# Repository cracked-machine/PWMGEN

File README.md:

# PWMGEN

## Handheld STM32 PWM Generator

* A 10mm x 10mm x 30mm PWM signal generator with duty, prescaler and frequency control. 
* Supports both 3.3v and 5v logic level outputs.
* Output PWM can source 500mA.
* Requires a 9VDC 600mA power supply (5.5mm x 2.1mm connector, Centre-Positive).

### TODO

* 5V PSU input (remove uA78M05C)
* Increase PWM source current capabilities. (Use bigger series pass transistor and regulators)
* Improve prescaler control input (use N-times throw switch and N-times GPIO input)

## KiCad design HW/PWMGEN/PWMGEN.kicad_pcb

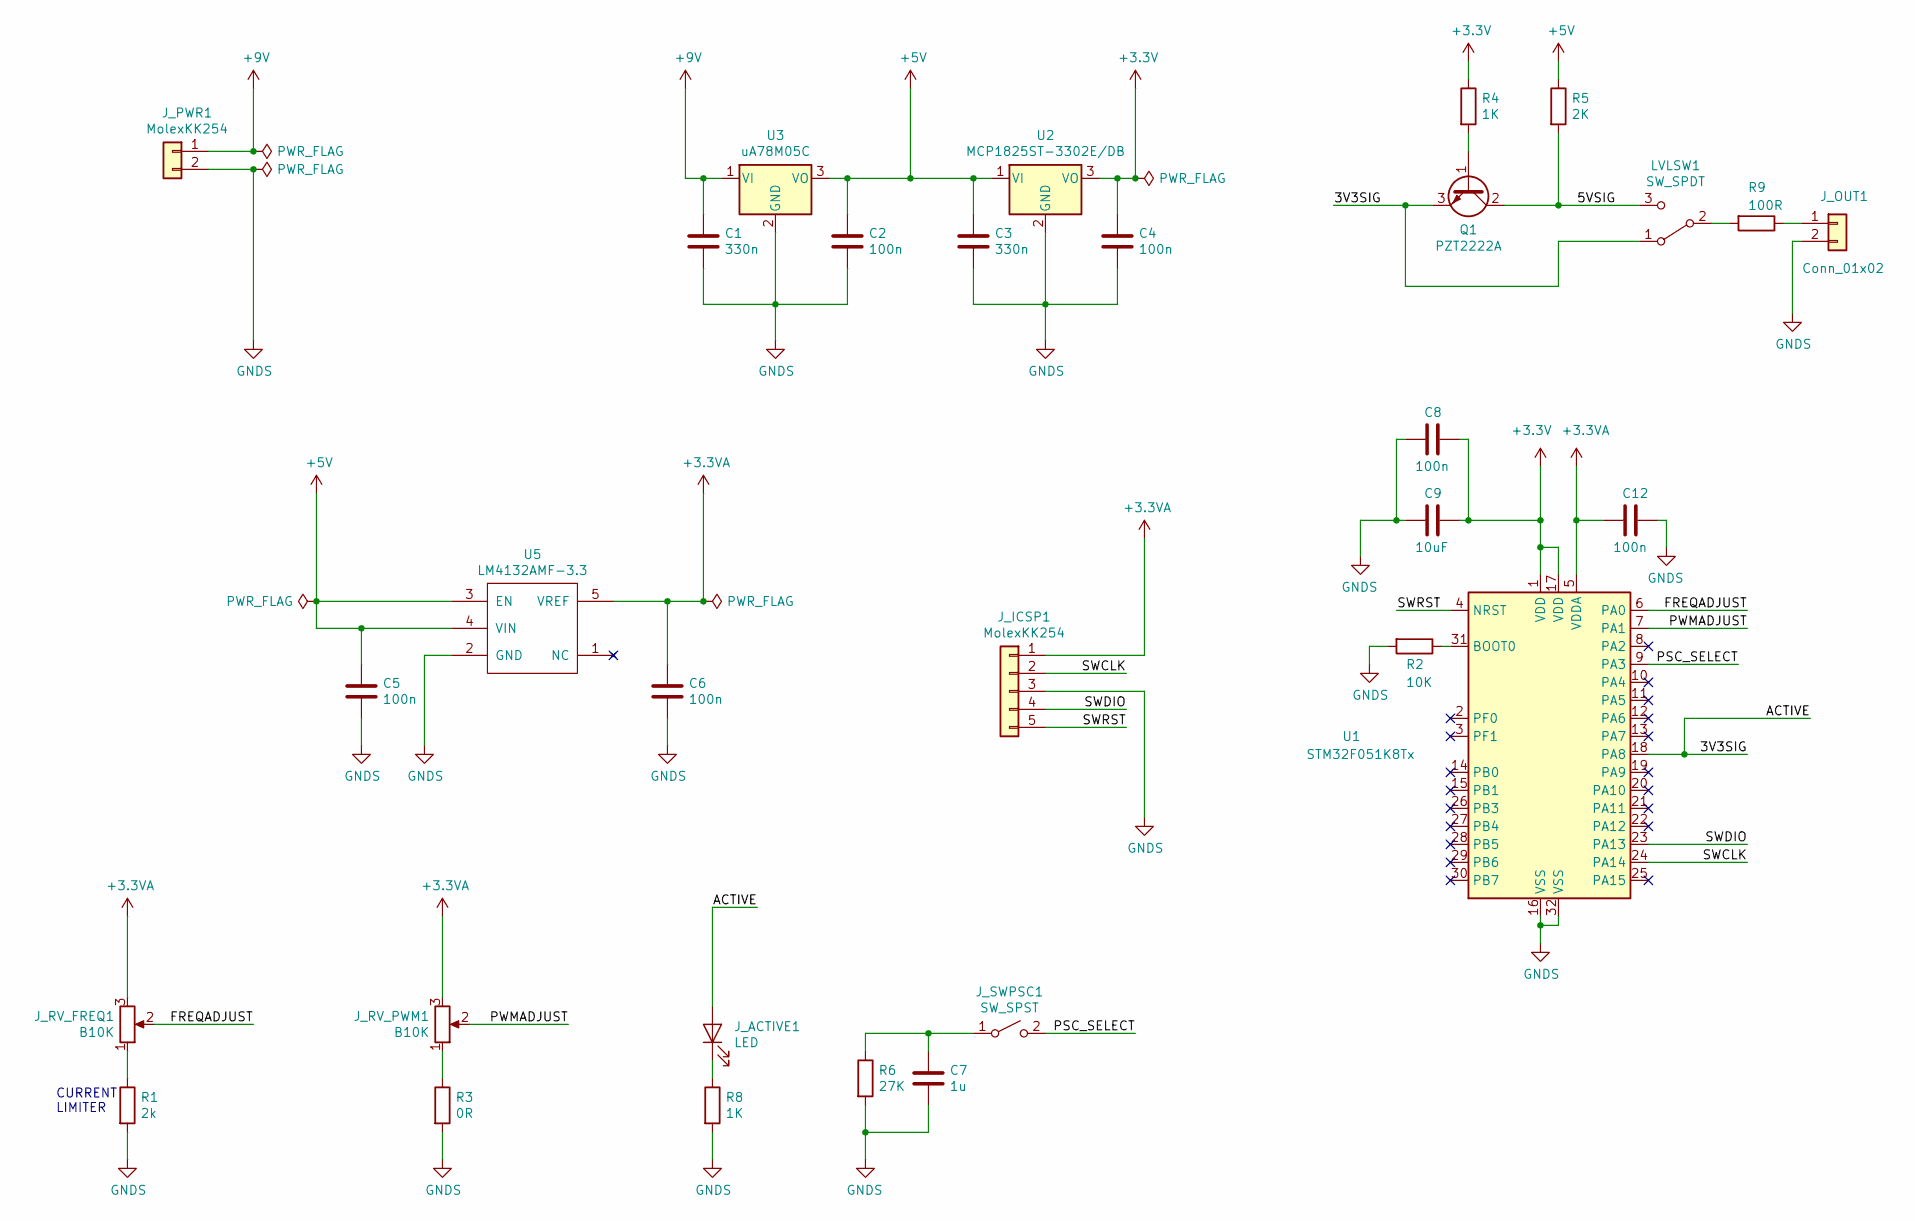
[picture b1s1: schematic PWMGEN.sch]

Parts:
C1, C3: 330n; C_1206_3216Metric_Pad1.42x1.75mm_HandSolder
C2, C4, C5, C6, C8, C12: 100n; C_1206_3216Metric_Pad1.42x1.75mm_HandSolder
C7: 1u; C_1206_3216Metric_Pad1.42x1.75mm_HandSolder
C9: 10uF; C_1206_3216Metric_Pad1.42x1.75mm_HandSolder
J_ACTIVE1: LED; PinHeader_1x02_P2.54mm_Vertical
J_ICSP1: MolexKK254; PinHeader_1x05_P2.54mm_Vertical
J_OUT1: Conn_01x02; PinHeader_1x02_P2.54mm_Vertical
J_PWR1: MolexKK254; PinHeader_1x02_P2.54mm_Vertical
J_RV_FREQ1: B10K; PinHeader_1x03_P2.54mm_Vertical
J_RV_PWM1: B10K; PinHeader_1x03_P2.54mm_Vertical
J_SWPSC1: SW_SPST; PinHeader_1x02_P2.54mm_Vertical
LVLSW1: SW_SPDT; PinHeader_1x03_P2.54mm_Vertical
Q1: PZT2222A; SOT-223
R1: 2k; R_1206_3216Metric_Pad1.42x1.75mm_HandSolder
R2: 10K; R_1206_3216Metric_Pad1.42x1.75mm_HandSolder
R3: 0R; R_1206_3216Metric_Pad1.42x1.75mm_HandSolder
R4, R8: 1K; R_1206_3216Metric_Pad1.42x1.75mm_HandSolder
R5: 2K; R_1206_3216Metric_Pad1.42x1.75mm_HandSolder
R6: 27K; R_1206_3216Metric_Pad1.42x1.75mm_HandSolder
R9: 100R; R_1206_3216Metric_Pad1.42x1.75mm_HandSolder
U1: STM32F051K8Tx; LQFP-32_7x7mm_P0.8mm
U2: MCP1825ST-3302E/DB; SOT-223-3_TabPin2
U3: uA78M05C; SOT-223-3_TabPin2
U5: LM4132AMF-3.3; SOT-23-5_HandSoldering

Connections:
+3.3VA: C6.1, C12.2, J_ICSP1.1, J_RV_FREQ1.3, J_RV_PWM1.3, U1.5 (VDDA), U5.5 (VREF)
+3V3: C4.1, C8.1, C9.1, R4.1, U1.1 (VDD), U1.17 (VDD), U2.3 (VO)
+5V: C2.1, C3.1, C5.1, R5.1, U2.1 (VI), U3.3 (VO), U5.3 (EN), U5.4 (VIN)
+9V: C1.1, J_PWR1.1, U3.1 (VI)
/3V3SIG: J_ACTIVE1.2 (A), LVLSW1.1 (A), Q1.3 (E), U1.18 (PA8)
/5VSIG: LVLSW1.3 (C), Q1.2 (C), R5.2
/FREQADJUST: J_RV_FREQ1.2, U1.6 (PA0)
/PSC_SELECT: J_SWPSC1.2 (B), U1.9 (PA3)
/PWMADJUST: J_RV_PWM1.2, U1.7 (PA1)
/SWCLK: J_ICSP1.2, U1.24 (PA14)
/SWDIO: J_ICSP1.4, U1.23 (PA13)
/SWRST: J_ICSP1.5, U1.4 (NRST)
GNDS: C1.2, C2.2, C3.2, C4.2, C5.2, C6.2, C7.2, C8.2, C9.2, C12.1, J_ICSP1.3, J_OUT1.2, J_PWR1.2, R1.2, R2.2, R3.2, R6.2, R8.2, U1.16 (VSS), U1.32 (VSS), U2.2 (GND), U3.2 (GND), U5.2 (GND)
unnamed: C7.1, J_SWPSC1.1 (A), R6.1
unnamed: J_ACTIVE1.1 (K), R8.1
unnamed: J_OUT1.1, R9.1
unnamed: J_RV_FREQ1.1, R1.1
unnamed: J_RV_PWM1.1, R3.1
unnamed: LVLSW1.2 (B), R9.2
unnamed: Q1.1 (B), R4.2
unnamed: R2.1, U1.31 (BOOT0)

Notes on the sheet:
CURRENT LIMITER

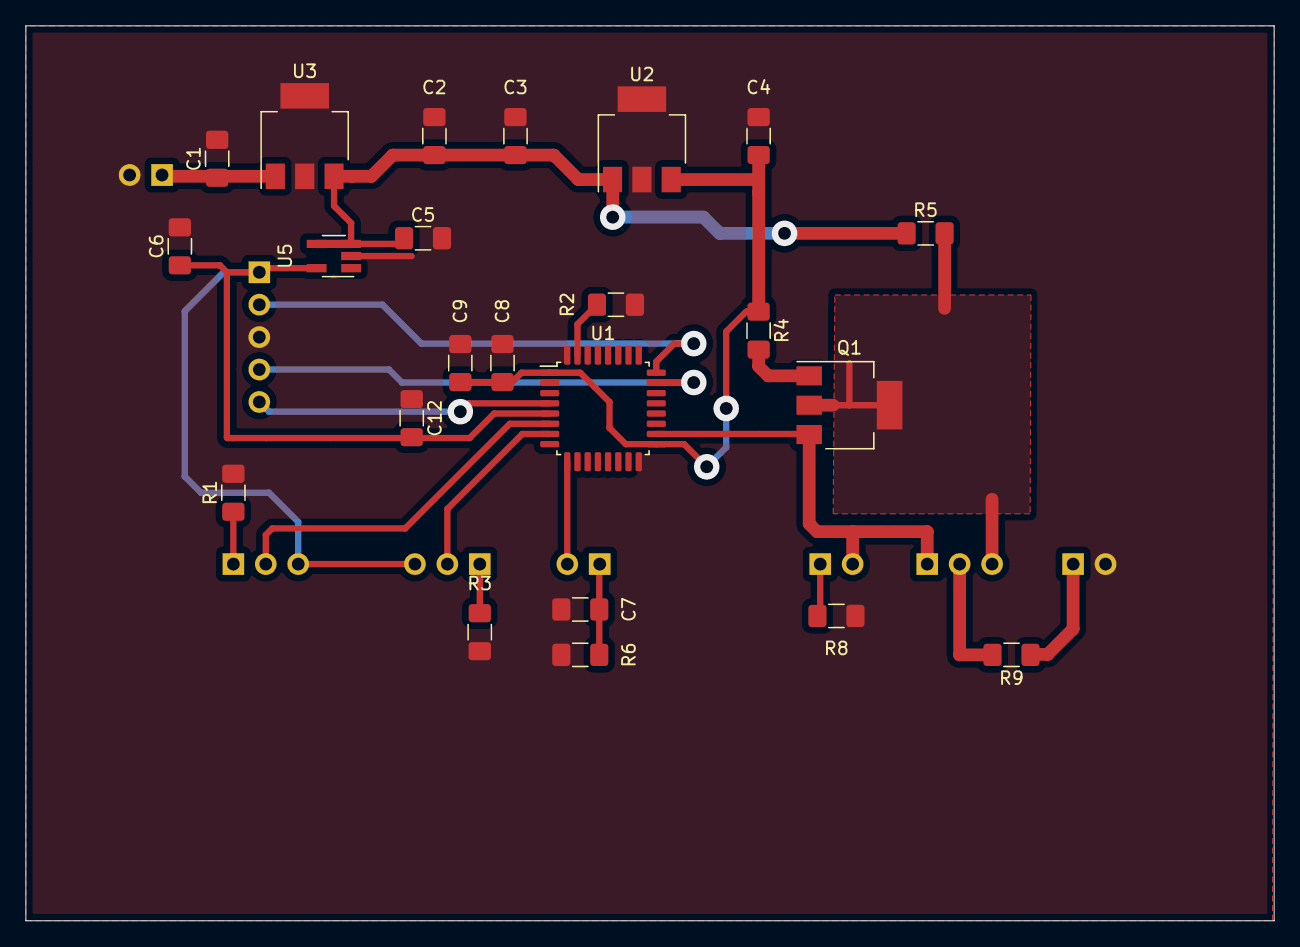
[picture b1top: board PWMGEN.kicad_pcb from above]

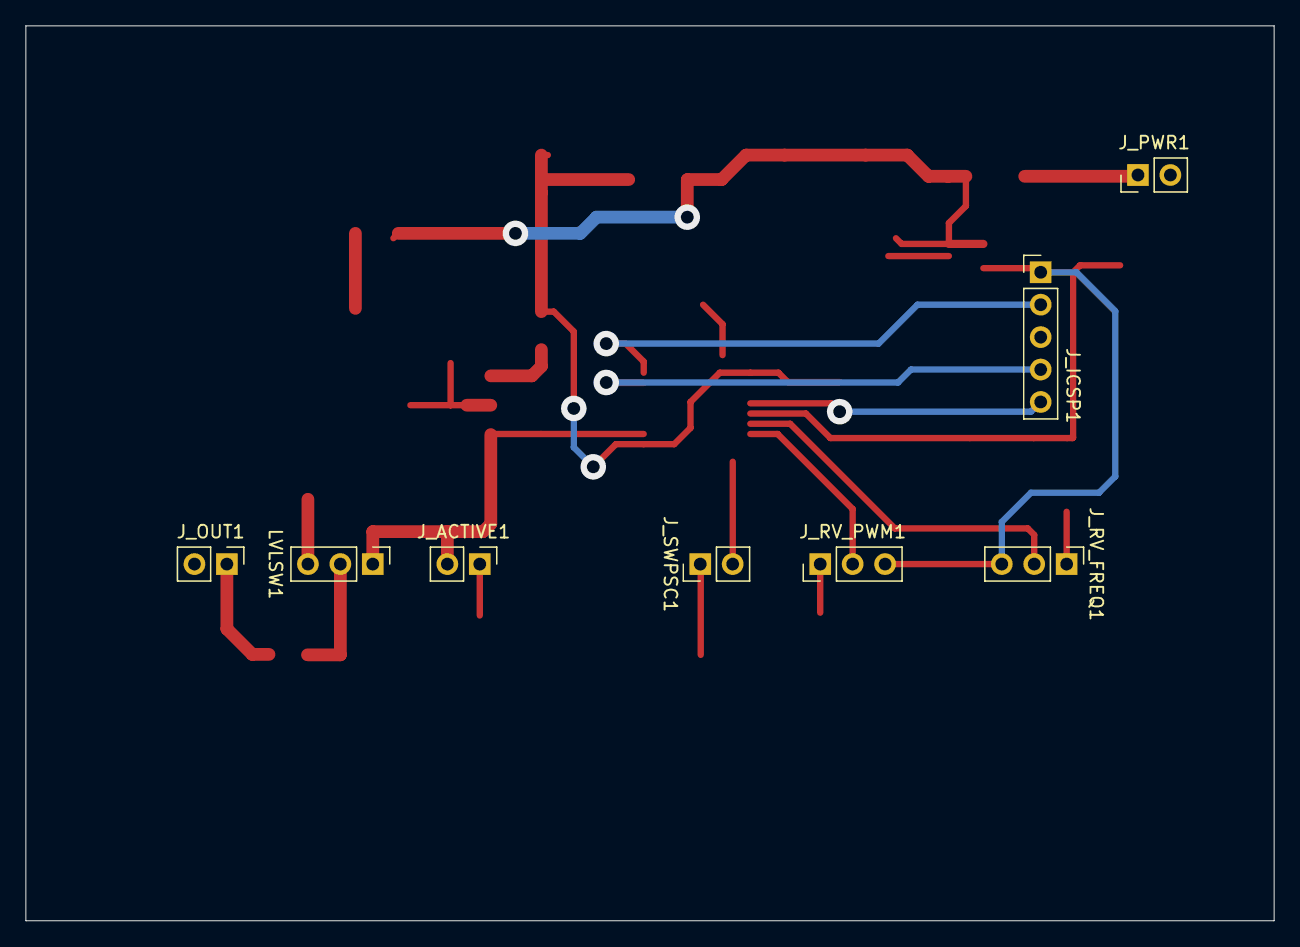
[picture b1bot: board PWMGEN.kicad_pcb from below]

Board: 2 copper layers, 97.8 x 70.1 mm, 31 parts (8 on the bottom side), 21 nets.

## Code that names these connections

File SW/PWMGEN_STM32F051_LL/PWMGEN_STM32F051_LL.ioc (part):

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Mcu.Name=STM32F051K8Tx
Mcu.Package=LQFP32
Mcu.UserName=STM32F051K8Tx
PA0.Mode=IN0
PA0.Signal=ADC_IN0
PA1.Mode=IN1
PA1.Signal=ADC_IN1
PA13.Mode=Serial_Wire
PA13.Signal=SYS_SWDIO
PA14.Mode=Serial_Wire
PA14.Signal=SYS_SWCLK
PA3.GPIOParameters=GPIO_PuPd,GPIO_ModeDefaultEXTI
PA3.GPIO_ModeDefaultEXTI=GPIO_MODE_IT_FALLING
PA3.GPIO_PuPd=GPIO_PULLUP
PA3.Signal=GPXTI3
PA8.Signal=S_TIM1_CH1
RCC.SYSCLKFreq_VALUE=48000000
RCC.SYSCLKSource=RCC_SYSCLKSOURCE_PLLCLK
board=custom

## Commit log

2019-10-04 updated layout
2019-10-06 updated MCU, layout, sw
    - Changed from STM32L011D4 to STM32F051K8
2019-10-10 updated sw
2019-10-11 updated sw
    - Implemented timers using LL
    - ADC/DMA using HAL
2019-12-01 updated schematic docs
